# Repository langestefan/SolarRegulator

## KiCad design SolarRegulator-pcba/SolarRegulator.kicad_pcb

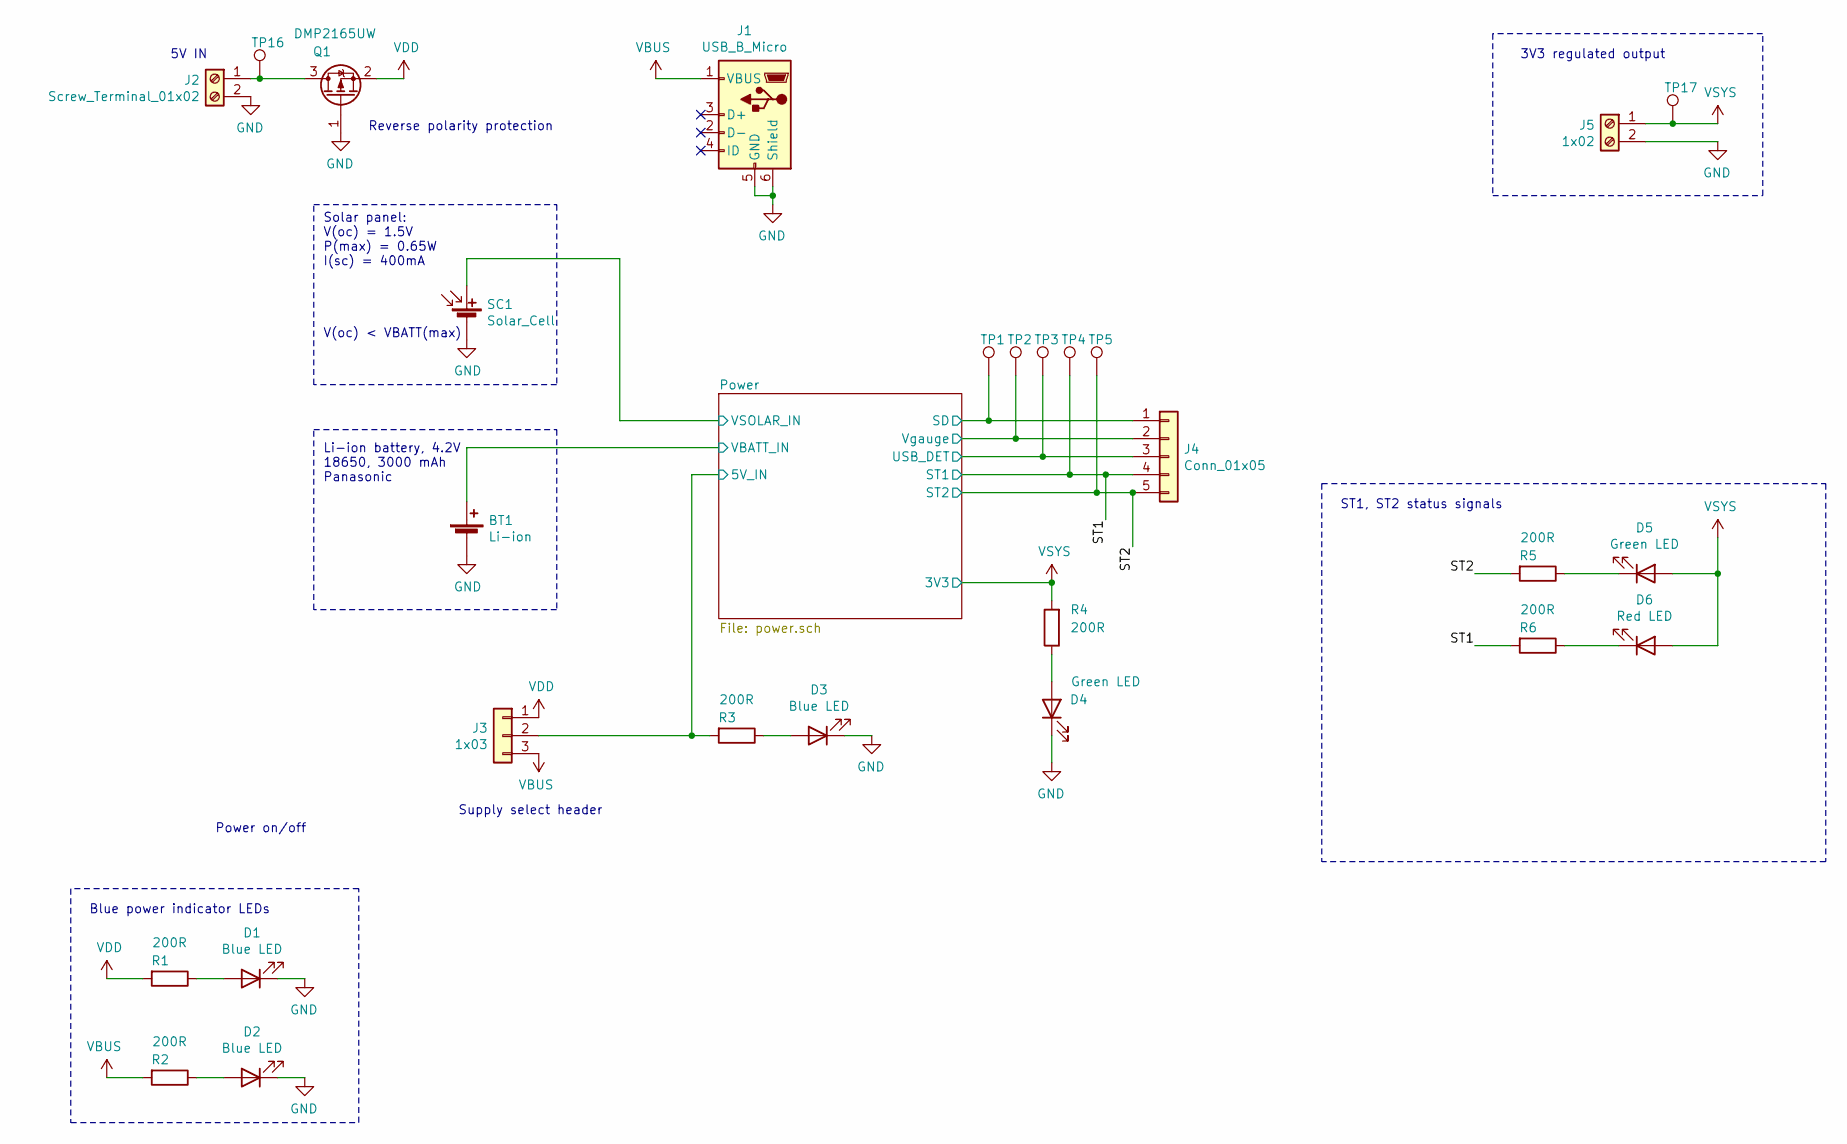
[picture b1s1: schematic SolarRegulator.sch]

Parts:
BT1: Li-ion; TerminalBlock_Phoenix_MKDS-1,5-2-5.08_1x02_P5.08mm_Horizont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
D1, D2, D3: Blue LED; LED_1206_3216Metric
D4, D5: Green LED; LED_1206_3216Metric
D6: Red LED; LED_1206_3216Metric
J1: USB_B_Micro; USB_Micro-B_Molex-105017-0001
J2: Screw_Terminal_01x02; TerminalBlock_Phoenix_MKDS-1,5-2-5.08_1x02_P5.08mm_Horizont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
J3: 1x03; PinHeader_1x03_P2.54mm_Vertical
J4: Conn_01x05; PinHeader_1x05_P2.54mm_Vertical
J5: 1x02; TerminalBlock_Phoenix_MKDS-1,5-2-5.08_1x02_P5.08mm_Horizont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
Q1: DMP2165UW; SOT-323_SC-70_Handsoldering
R1, R2, R3, R4, R5, R6: 200R; R_1206_3216Metric_Pad1.42x1.75mm_HandSolder
SC1: Solar_Cell; TerminalBlock_Phoenix_MKDS-1,5-2-5.08_1x02_P5.08mm_Horizont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
TP1, TP2, TP3, TP4, TP5, TP16, TP17: TestPoint; TestPoint_Pad_D1.0mm

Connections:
+BATT: BT1.1 (+); also elsewhere on the board
/Power/5V_IN: J3.2, R3.2; also elsewhere on the board
/Power/SD: J4.1, TP1.1; also elsewhere on the board
/Power/USB_DET: J4.3, TP3.1; also elsewhere on the board
/Power/VSOLAR_IN: SC1.1 (+); also elsewhere on the board
/Power/Vgauge: J4.2, TP2.1; also elsewhere on the board
/ST1: J4.4, R6.2, TP4.1; also elsewhere on the board
/ST2: J4.5, R5.2, TP5.1; also elsewhere on the board
GND: BT1.2 (-), D1.1 (K), D2.1 (K), D3.1 (K), D4.1 (K), J1.5 (GND), J1.6 (Shield), J2.2, J5.2, Q1.1 (G), SC1.2 (-); also elsewhere on the board
unnamed: D1.2 (A), R1.1
unnamed: D2.2 (A), R2.1
unnamed: D3.2 (A), R3.1
unnamed: D4.2 (A), R4.1
unnamed: D5.1 (K), R5.1
unnamed: D6.1 (K), R6.1
unnamed: J2.1, Q1.3 (D), TP16.1
VBUS: J1.1 (VBUS), J3.3, R2.2; also elsewhere on the board
VDD: D5.2 (A), D6.2 (A), J3.1, J5.1, Q1.2 (S), R1.2, R4.2, TP17.1; also elsewhere on the board

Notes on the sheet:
5V IN
Supply select header
Reverse polarity protection
Power on/off
3V3 regulated output
Blue power indicator LEDs
ST1, ST2 status signals
Solar panel: V(oc) = 1.5V P(max) = 0.65W I(sc) = 400mA
V(oc) < VBATT(max)
Li-ion battery, 4.2V 18650, 3000 mAh Panasonic

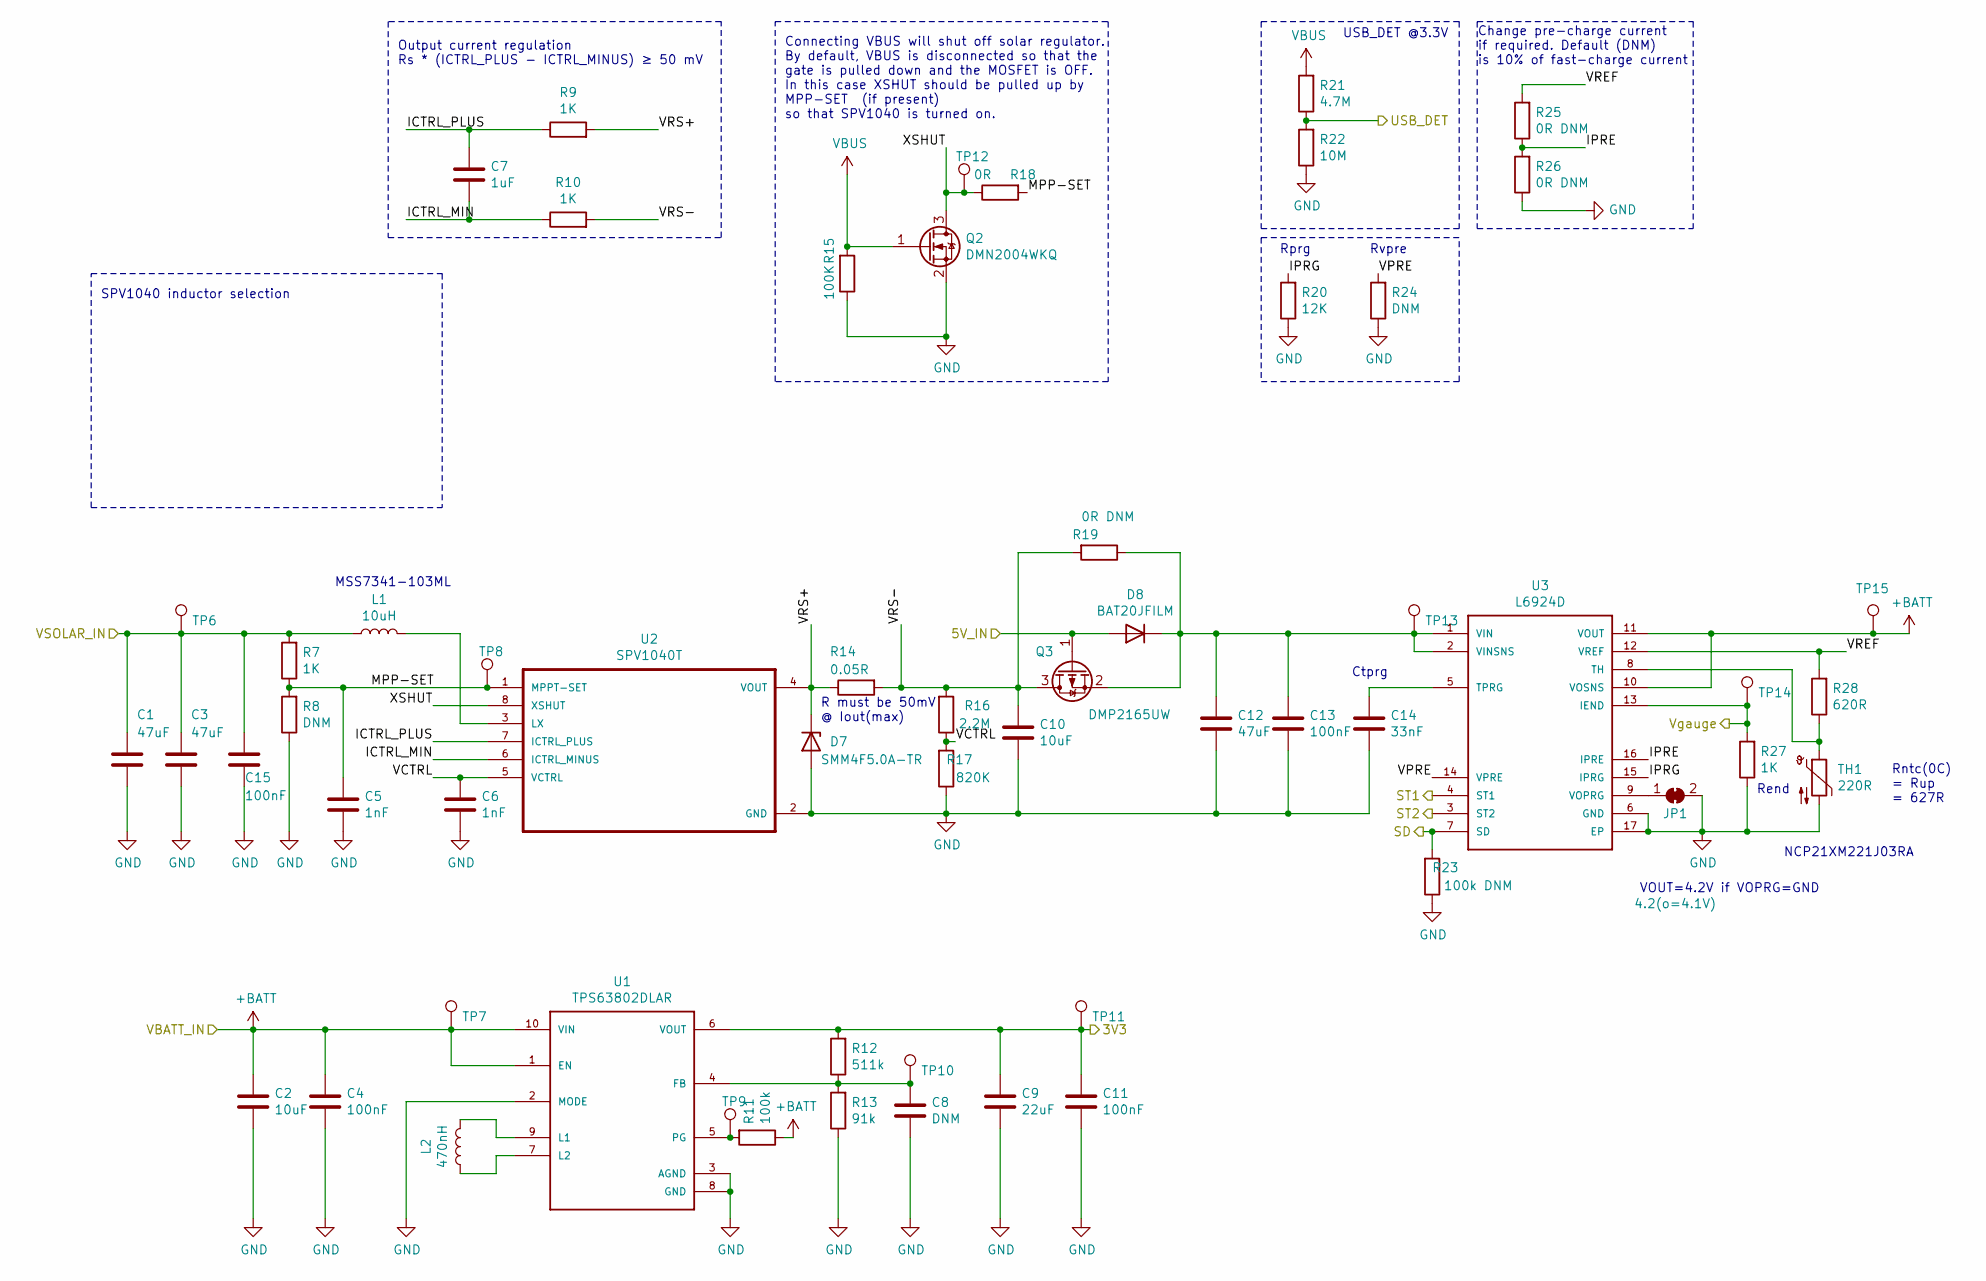
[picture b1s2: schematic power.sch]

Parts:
C1, C3, C12: 47uF; C_1206_3216Metric_Pad1.42x1.75mm_HandSolder
C2, C10: 10uF; C_0805_2012Metric_Pad1.15x1.40mm_HandSolder
C4, C11, C13, C15: 100nF; C_0805_2012Metric_Pad1.15x1.40mm_HandSolder
C5, C6: 1nF; C_0805_2012Metric_Pad1.15x1.40mm_HandSolder
C7: 1uF; C_1206_3216Metric_Pad1.42x1.75mm_HandSolder
C8: DNM; C_0805_2012Metric_Pad1.15x1.40mm_HandSolder
C9: 22uF; C_0805_2012Metric_Pad1.15x1.40mm_HandSolder
C14: 33nF; C_0805_2012Metric_Pad1.15x1.40mm_HandSolder
D7: SMM4F5.0A-TR; SMM4FxxA
D8: BAT20JFILM; D_SOD-323_HandSoldering
JP1: 4.2(o=4.1V); SolderJumper-2_P1.3mm_Bridged_RoundedPad1.0x1.5mm
L1: 10uH; MSS7341-103ML
L2: 470nH; Coilcraft-XFL4015
Q2: DMN2004WKQ; SOT-323_SC-70_Handsoldering
Q3: DMP2165UW; SOT-323_SC-70_Handsoldering
R7, R9, R10, R27: 1K; R_1206_3216Metric_Pad1.42x1.75mm_HandSolder
R8, R24: DNM; R_1206_3216Metric_Pad1.42x1.75mm_HandSolder
R11: 100k; R_1206_3216Metric_Pad1.42x1.75mm_HandSolder
R12: 511k; R_1206_3216Metric_Pad1.42x1.75mm_HandSolder
R13: 91k; R_1206_3216Metric_Pad1.42x1.75mm_HandSolder
R14: 0.05R; R_1206_3216Metric_Pad1.42x1.75mm_HandSolder
R15: 100K; R_1206_3216Metric_Pad1.42x1.75mm_HandSolder
R16: 2.2M; R_1206_3216Metric_Pad1.42x1.75mm_HandSolder
R17: 820K; R_1206_3216Metric_Pad1.42x1.75mm_HandSolder
R18: 0R; R_1206_3216Metric_Pad1.42x1.75mm_HandSolder
R19, R25, R26: 0R DNM; R_1206_3216Metric_Pad1.42x1.75mm_HandSolder
R20: 12K; R_1206_3216Metric_Pad1.42x1.75mm_HandSolder
R21: 4.7M; R_1206_3216Metric_Pad1.42x1.75mm_HandSolder
R22: 10M; R_1206_3216Metric_Pad1.42x1.75mm_HandSolder
R23: 100k DNM; R_1206_3216Metric_Pad1.42x1.75mm_HandSolder
R28: 620R; R_1206_3216Metric_Pad1.42x1.75mm_HandSolder
TH1: 220R; R_0805_2012Metric
TP6, TP7, TP8, TP9, TP10, TP11, TP12, TP13, TP14, TP15: TestPoint; TestPoint_Pad_D1.0mm
U1: TPS63802DLAR; VREG_TPS63802DLAR
U2: SPV1040T
U3: L6924D

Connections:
+BATT: C2.1, C4.1, R11.1, TP7.1, TP15.1, U1.1 (EN), U1.10 (VIN), U3.10 (VOSNS), U3.11 (VOUT); also elsewhere on the board
/Power/5V_IN: D8.2 (A), Q3.1 (G); also elsewhere on the board
/Power/ICTRL_MIN: C7.2, R10.1, U2.6 (ICTRL_MINUS)
/Power/ICTRL_PLUS: C7.1, R9.1, U2.7 (ICTRL_PLUS)
/Power/IPRE: R25.1, R26.2, U3.16 (IPRE)
/Power/IPRG: R20.2, U3.15 (IPRG)
/Power/MPP-SET: C5.1, R7.1, R8.2, R18.2, TP8.1, U2.1 (MPPT-SET)
/Power/SD: R23.2, U3.7 (SD); also elsewhere on the board
/Power/USB_DET: R21.1, R22.2; also elsewhere on the board
/Power/VCTRL: C6.1, R16.1, R17.2, U2.5 (VCTRL)
/Power/VPRE: R24.2, U3.14 (VPRE)
/Power/VREF: R25.2, R28.2, U3.12 (VREF)
/Power/VRS+: D7.1 (K), R9.2, R14.1, U2.4 (VOUT)
/Power/VRS-: C10.1, Q3.3 (D), R10.2, R14.2, R16.2, R19.2
/Power/VSOLAR_IN: C1.1, C3.1, C15.1, L1.1, R7.2, TP6.1; also elsewhere on the board
/Power/Vgauge: R27.2, TP14.1, U3.13 (IEND); also elsewhere on the board
/Power/XSHUT: Q2.3 (D), R18.1, TP12.1, U2.8 (XSHUT)
/ST1: U3.4 (ST1); also elsewhere on the board
/ST2: U3.3 (ST2); also elsewhere on the board
GND: C1.2, C2.2, C3.2, C4.2, C5.2, C6.2, C8.2, C9.2, C10.2, C11.2, C12.2, C13.2, C14.2, C15.2, D7.2 (A), JP1.2 (B), Q2.2 (S), R8.1, R13.1, R15.1, R17.1, R20.1, R22.1, R23.1, R24.1, R26.1, R27.1, TH1.2, U1.2 (MODE), U1.3 (AGND), U1.8 (GND), U2.2 (GND), U3.6 (GND), U3.17 (EP); also elsewhere on the board
unnamed: C8.1, R12.1, R13.2, TP10.1, U1.4 (FB)
unnamed: C12.1, C13.1, D8.1 (K), Q3.2 (S), R19.1, TP13.1, U3.1 (VIN), U3.2 (VINSNS)
unnamed: C14.1, U3.5 (TPRG)
unnamed: JP1.1 (A), U3.9 (VOPRG)
unnamed: L1.2, U2.3 (LX)
unnamed: L2.1, U1.7 (L2)
unnamed: L2.2, U1.9 (L1)
unnamed: R11.2, TP9.1, U1.5 (PG)
unnamed: R28.1, TH1.1, U3.8 (TH)
VBUS: Q2.1 (G), R15.2, R21.2; also elsewhere on the board
VDD: C9.1, C11.1, R12.2, TP11.1, U1.6 (VOUT); also elsewhere on the board

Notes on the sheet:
Connecting VBUS will shut off solar regulator. By default, VBUS is disconnected so that the gate is pulled down and the MOSFET is OFF. In this case XSHUT should be pulled up by MPP-SET (if present) so that SPV1040 is turned on.
R must be 50mV @ Iout(max)
MSS7341-103ML
USB_DET @3.3V
VOUT=4.2V if VOPRG=GND
Change pre-charge current if required. Default (DNM) is 10% of fast-charge current
Output current regulation Rs * (ICTRL_PLUS - ICTRL_MINUS) ≥ 50 mV
SPV1040 inductor selection
Rprg
Rvpre
Rend
Ctprg
NCP21XM221J03RA
Rntc(0C) = Rup = 627R

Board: 2 copper layers, 85 parts (0 on the bottom side), 38 nets, no tracks yet.

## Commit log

2020-08-17 Add terminal blocks
2020-08-19 Add more footprints to schematic and pcb
2020-08-19 Revert old state
2020-08-19 Modify power.sch
2020-08-19 Add final footprints, update LED footprints to 1206
